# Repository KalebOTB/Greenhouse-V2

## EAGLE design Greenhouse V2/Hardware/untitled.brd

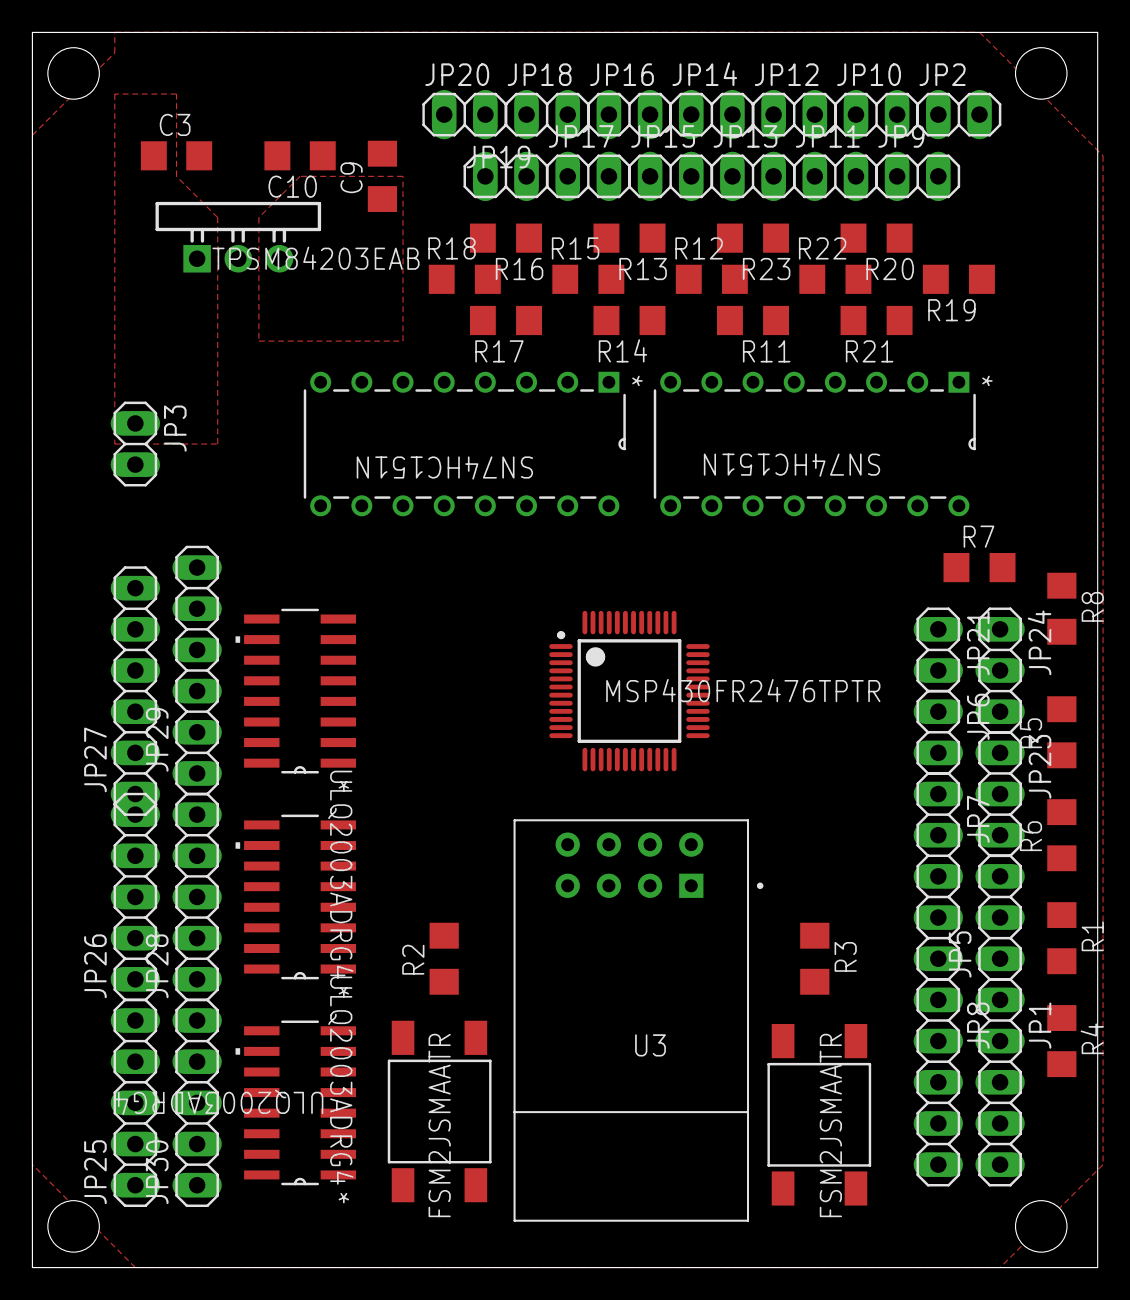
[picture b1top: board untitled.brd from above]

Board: 2 copper layers, 65.7 x 76.2 mm, 62 parts (0 on the bottom side), 68 nets, no tracks yet.

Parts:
C3: 10uF; C1206
C9, C10: 47uF; C1206
JP1, JP7, JP8, JP25, JP26, JP28, JP30: 1X05
JP2, JP3, JP6, JP9, JP10, JP11, JP12, JP13, JP14, JP15, JP16, JP17, JP18, JP19, JP20, JP21: 1X02
JP5, JP23, JP24: 1X03
JP27, JP29: 1X06
R1, R6, R7: 1K; R1206
R2, R3, R11, R12, R13, R14, R15, R16, R17, R18, R19, R20, R21, R22, R23: 10k; R1206
R4, R5, R8: 5k; R1206
U1: MSP430FR2476TPTR; PT0048A_N
U2, U6, U7: ULQ2003ADRG4; D16
U3: ESP8266-01/ESP-01; XCVR_ESP8266-01/ESP-01
U4, U5: SN74HC151N; N16
U9: TPSM84203EAB; EAB0003A
U10, U12: FSM2JSMAATR; SWITCH_FSM2JSMAA_TYC

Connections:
12V_VCC: C3.1, JP3.1, JP25.1, JP25.2, JP25.3, JP25.4, JP25.5, JP26.1, JP26.2, JP26.3, JP26.4, JP26.5, JP27.1, JP27.2, JP27.3, JP27.4, JP27.5, JP27.6, U2.9, U6.9, U7.9, U9.1
+3V3: C9.1, JP1.5, JP5.2, JP7.5, JP8.5, JP23.2, JP24.2, R2.2, R3.1, U1.1, U3.6, U3.8, U9.3
A1RXD: JP21.2, U1.29, U3.5
A1TXD: JP21.1, U1.30, U3.4
GND: C3.2, C10.2, JP1.3, JP3.2, JP5.3, JP7.3, JP8.3, JP23.3, JP24.3, R4.2, R5.2, R8.2, R11.2, R12.2, R13.2, R14.2, R15.2, R16.2, R17.2, R18.2, R19.2, R20.2, R21.2, R22.2, R23.2, U1.48, U2.8, U3.1, U4.7, U4.8, U5.7, U5.8, U5.12, U5.13, U5.14, U6.8, U7.8, U9.2, U10.1, U10.2, U12.1, U12.2
unnamed: R3.2, U3.7, U12.3, U12.4
unnamed: JP18.1, R16.1, U4.2
unnamed: JP19.1, R17.1, U4.3
unnamed: JP13.1, R11.1, U4.12
unnamed: C9.2, C10.1
unnamed: JP14.1, R12.1, U4.13
unnamed: JP15.1, R13.1, U4.14
unnamed: JP16.1, R14.1, U4.15
unnamed: JP5.1, R1.2, R4.1
unnamed: JP23.1, R5.1, R6.2
unnamed: JP24.1, R7.2, R8.1
unnamed: JP20.1, R18.1, U4.4
unnamed: JP2.1, R19.1, U5.15
unnamed: JP12.1, R23.1, U5.4
unnamed: JP9.1, R20.1, U5.1
unnamed: JP10.1, R21.1, U5.2
unnamed: JP11.1, R22.1, U5.3
unnamed: JP17.1, R15.1, U4.1
OUT1: JP29.6, U2.16, U6.16, U7.16
OUT2: JP28.1, U2.14, U2.15
OUT3: JP28.2, U2.13
OUT4: JP28.3, U2.12
OUT5: JP28.4, U2.11
OUT6: JP28.5, U2.10
OUT7: JP29.1, U6.14, U6.15
OUT8: JP29.2, U6.13
OUT9: JP29.3, U6.12
OUT10: JP29.4, U6.11
OUT11: JP29.5, U6.10
OUT12: JP30.1, U7.14, U7.15
OUT13: JP30.2, U7.13
OUT14: JP30.3, U7.12
OUT15: JP30.4, U7.11
OUT16: JP30.5, U7.10
P1.0_A0: R1.1, U1.12
P1.6_A6: R6.1, U1.6
P1.7_A7: R7.1, U1.7
P2.0_I/O: U1.46, U4.11, U5.11
P2.1_I/O: U1.47, U4.10, U5.10
P2.2_I/O: U1.16, U4.9, U5.9
P3.0_I/O: JP1.4, JP7.4, JP8.4, U1.23, U7.1
P3.1_I/O: U1.27, U7.2, U7.3, U7.4
P3.2_I/O: U1.38, U7.5
P3.3_I/O: U1.24, U7.6
P3.4_I/O: U1.26, U7.7
P4.1_I/O: U1.34, U5.5
P4.2_I/O: U1.35, U4.5
P4.5_I/O: JP2.2, JP9.2, JP10.2, JP11.2, JP12.2, JP13.2, JP14.2, JP15.2, JP16.2, JP17.2, JP18.2, JP19.2, JP20.2, U1.17, U4.16, U5.16
P5.0_I/O: U1.43, U2.1
P5.1_I/O: U1.44, U2.2, U2.3, U2.4
P5.2_I/O: U1.45, U2.5
P5.3_I/O: U1.10, U2.6
P5.4_I/O: U1.11, U2.7
P5.6_I/O: U1.20, U6.2, U6.3, U6.4
P5.7_I/O: U1.21, U6.5
P6.0_I/O: U1.22, U6.6
P6.1_I/O: U1.40, U6.7
P6.2_I/O: U1.41, U6.1
PROG_MODE: R2.1, U1.25, U3.3, U10.3, U10.4
SBWTCK: JP6.2, U1.3
SBWTDIO: JP6.1, U1.2
UCB0SCL: JP1.1, JP7.1, JP8.1, U1.15
UCB0SDA: JP1.2, JP7.2, JP8.2, U1.14

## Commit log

2023-05-10 Add files via upload
    Init
2023-05-10 Moved files and added ESP code
2023-05-16 Moved Files

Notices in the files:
parts and their libraries:
COPYRIGHT: Copyright (C) 2023 Ultra Librarian. All rights reserved.
COPYRIGHT: Copyright (C) 2022 Ultra Librarian. All rights reserved.
